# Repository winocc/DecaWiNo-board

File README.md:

# DecaWiNo-board
This is the git repository of the DecaWiNo board

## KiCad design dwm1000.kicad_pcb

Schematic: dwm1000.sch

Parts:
D1: LED_RGB; LED_RGB_Cree-PLCC-6_6x5mm_P2.1mm
D2: LED_RCGB; LED_D5.0mm-4
DWM1: DWM1000
J1, J6, J7: CONN_01X02; Pin_Header_Straight_1x02_Pitch2.54mm
J2, J3, J11, J12: CONN_01X05; Pin_Header_Straight_1x05_Pitch2.54mm
J4, J5: CONN_01X14; Pin_Header_Straight_1x14_Pitch2.54mm
J8: CONN_01X01; Pin_Header_Straight_1x01_Pitch2.54mm
J9: CONN_01X03; Pin_Header_Straight_1x03_Pitch2.54mm
J10: CONN_01X08; Pin_Header_Straight_1x08_Pitch2.54mm
R1, R2, R3, R4: R; R_1206_HandSoldering

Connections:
/A2: J4.2, J5.2
/A3: J4.3, J5.3
/A4: J4.4, J5.4, R1.1
/A5: J4.5, J5.5, R2.1
/A6: J4.6, J5.6, R3.1
/A7: J4.7, J5.7, R4.1
/A8: J4.8, J5.8
/A9: J4.9, J5.9
/A10: J4.10, J5.10
/B1: J1.1, J2.1, J3.1
/B2: J2.2, J3.2
/B4: J2.4, J3.4, R1.2
/B5: J2.5, J3.5
EXTON: DWM1.1 (EXTON), J11.1
GND: D1.4, D1.5, D1.6, D2.2, DWM1.2 (WAKEUP), DWM1.8 (VSS), DWM1.16 (VSS), DWM1.21 (VSS), DWM1.23 (VSS), DWM1.24 (VSS), J1.2, J4.1, J5.1, J9.1, J10.6
GPIO0: DWM1.15 (GPIO0/RXOKLED), J12.5
GPIO1: DWM1.14 (GPIO1/SFDLED), J12.4
GPIO2: DWM1.13 (GPIO2/RXLED), J12.3
GPIO3: DWM1.12 (GPIO3/TXLED), J12.2
GPIO4: DWM1.11 (GPIO4/EXTPA), J12.1
GPIO5: DWM1.10 (GPIO5/EXTTXE/SPIPOL), J11.5
GPIO6: DWM1.9 (GPIO6/EXTRXE/SPIHA), J11.4
GPIO7: DWM1.4 (GPIO7), J11.3
IRQ: DWM1.22 (IRQ/GPIO8), J4.11, J5.11
unnamed: D1.1, D2.1, R4.2
unnamed: D1.2, D2.3, R3.2
unnamed: D1.3, D2.4, R2.2
unnamed: J7.2, J10.2
unnamed: J8.1, J10.3
unnamed: J6.1, J10.4
unnamed: J6.2, J10.5
unnamed: J9.3, J10.8
RSTn: DWM1.3 (RSTn), J11.2
SPICLK: DWM1.20 (SPICLK), J7.1, J10.1
SPICS: DWM1.17 (SPICSn), J4.12, J5.12
SPIMISO: DWM1.19 (SPIMISO), J4.14, J5.14
SPIMOSI: DWM1.18 (SPIMOSI), J4.13, J5.13
VCC: DWM1.5 (VDDAON), DWM1.6 (VDD3V3), DWM1.7 (VDD3V3), J2.3, J3.3, J9.2, J10.7

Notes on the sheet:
Power Pin
http://fr.farnell.com/cree/clp6c-fkb-cm1q1h1bb7r3r3/led-plcc6-multi-colour/dp/1855543

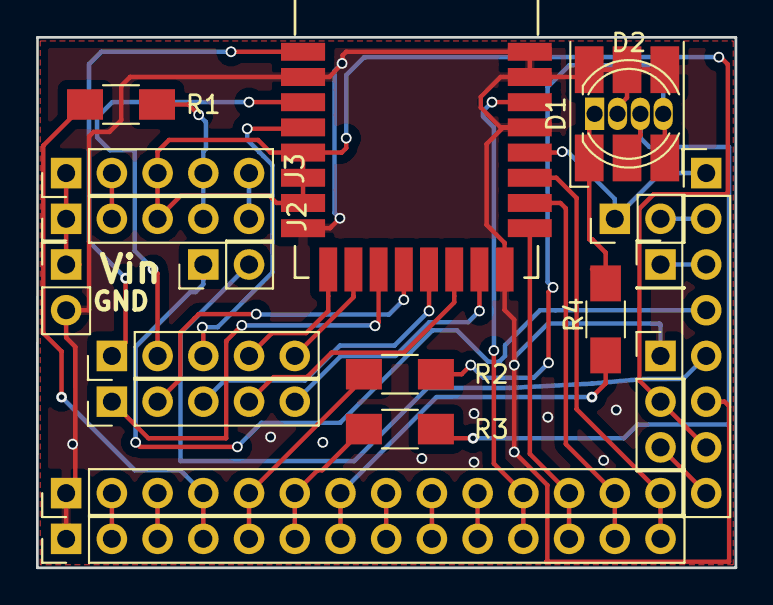
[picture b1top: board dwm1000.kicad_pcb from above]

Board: 2 copper layers, 38.8 x 29.5 mm, 19 parts (0 on the bottom side), 38 nets.

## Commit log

2018-01-22 correction of 2 missing connections on DW1000
2018-01-22 adding ground planes both sides
2018-02-06 Add LICENSE file
